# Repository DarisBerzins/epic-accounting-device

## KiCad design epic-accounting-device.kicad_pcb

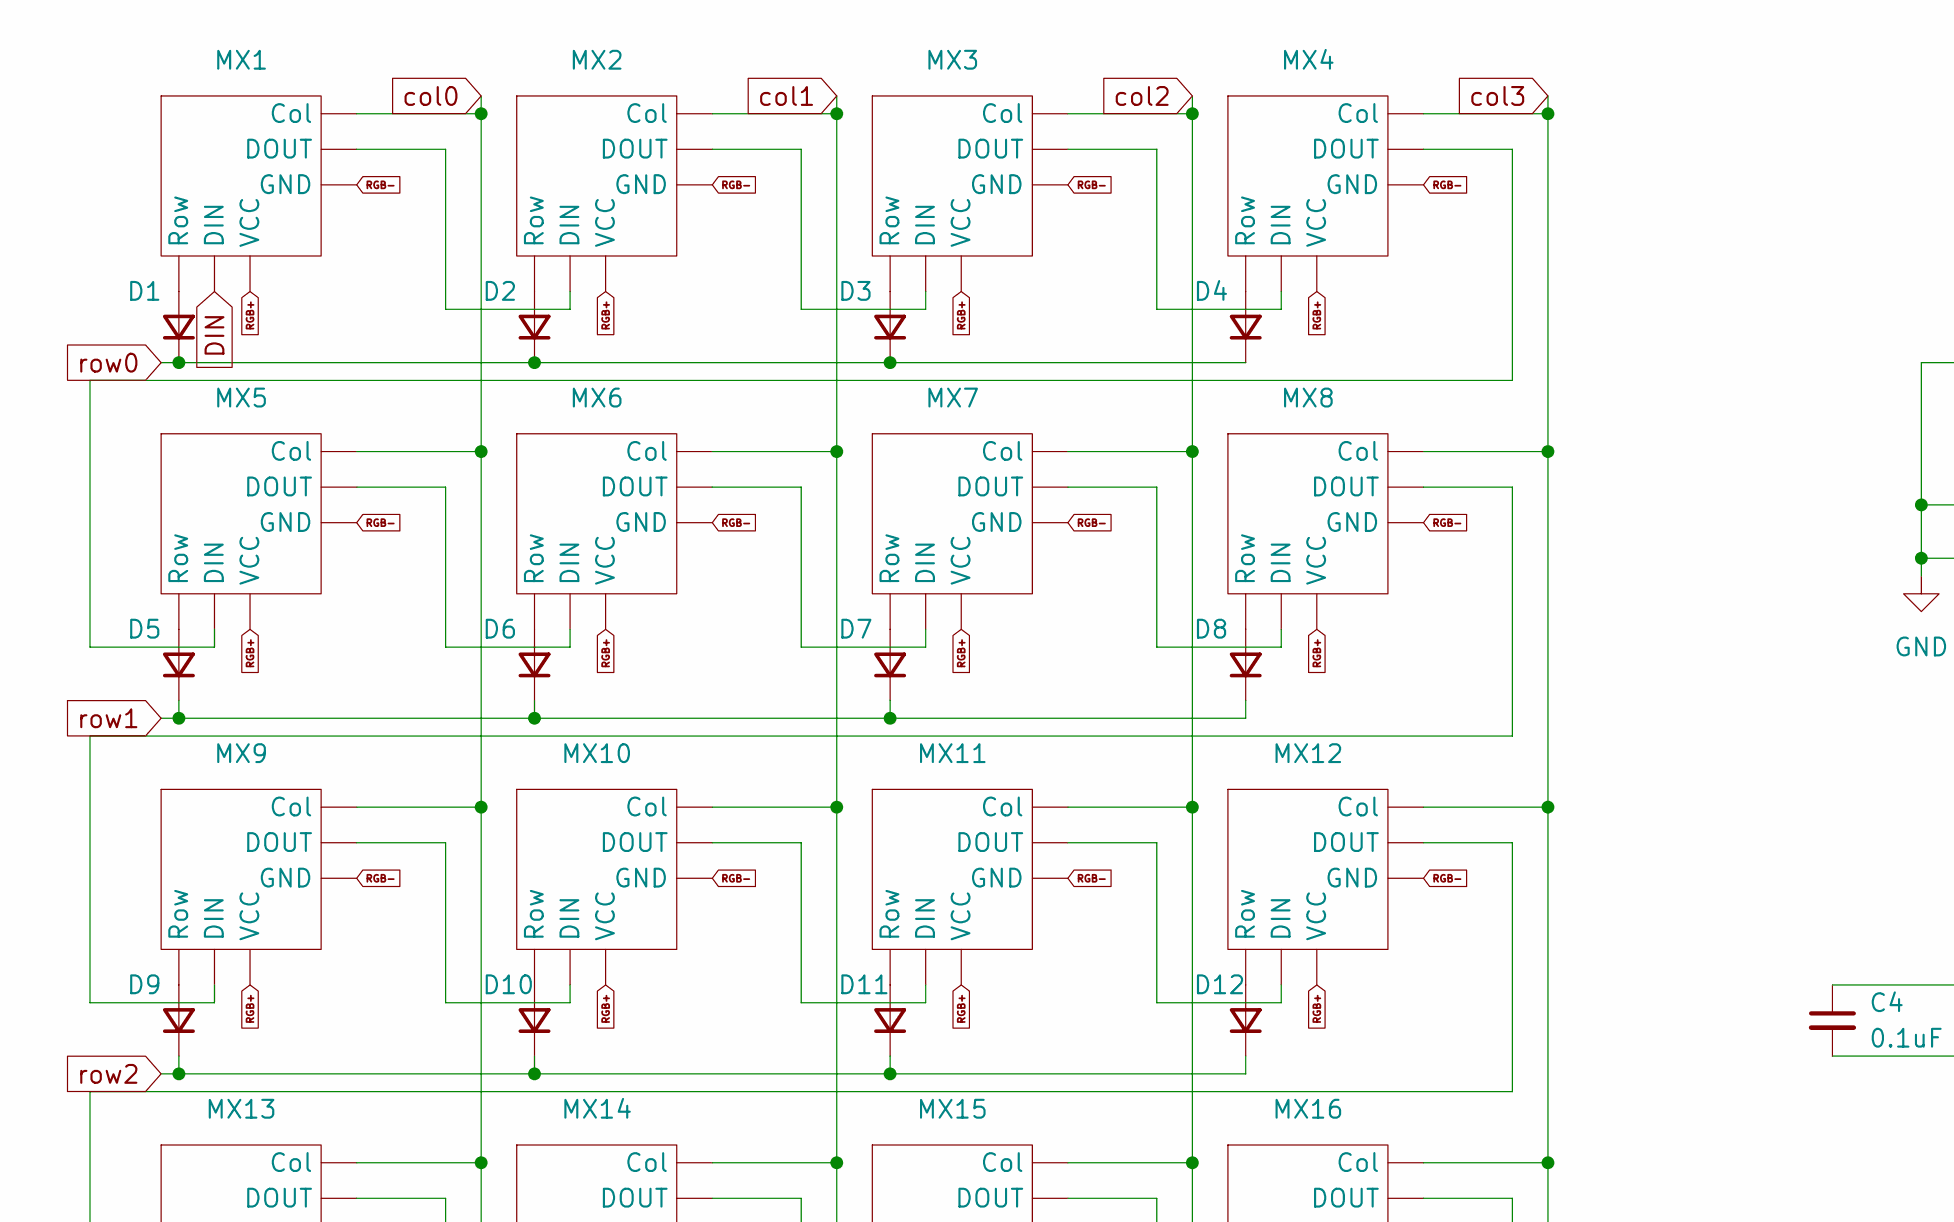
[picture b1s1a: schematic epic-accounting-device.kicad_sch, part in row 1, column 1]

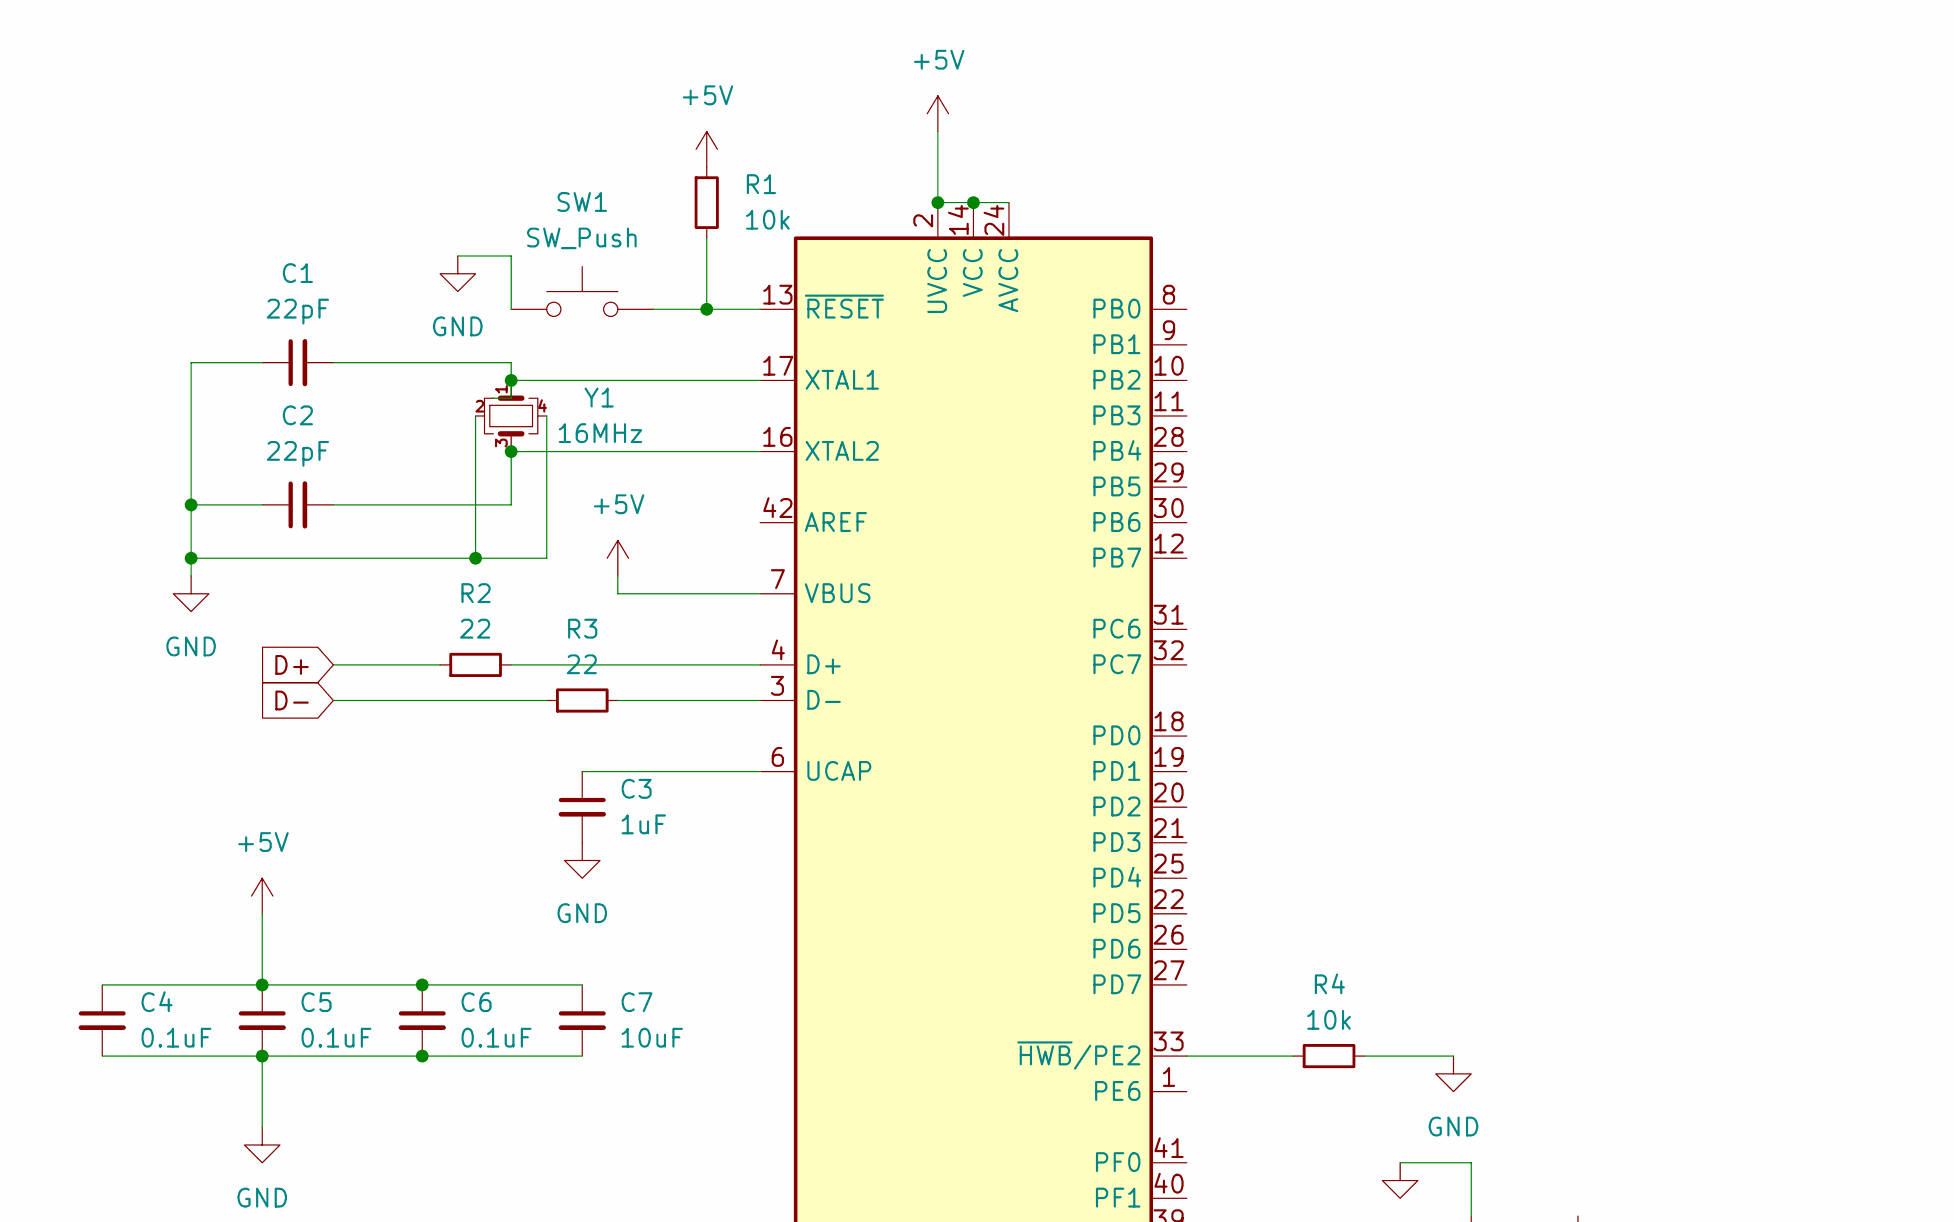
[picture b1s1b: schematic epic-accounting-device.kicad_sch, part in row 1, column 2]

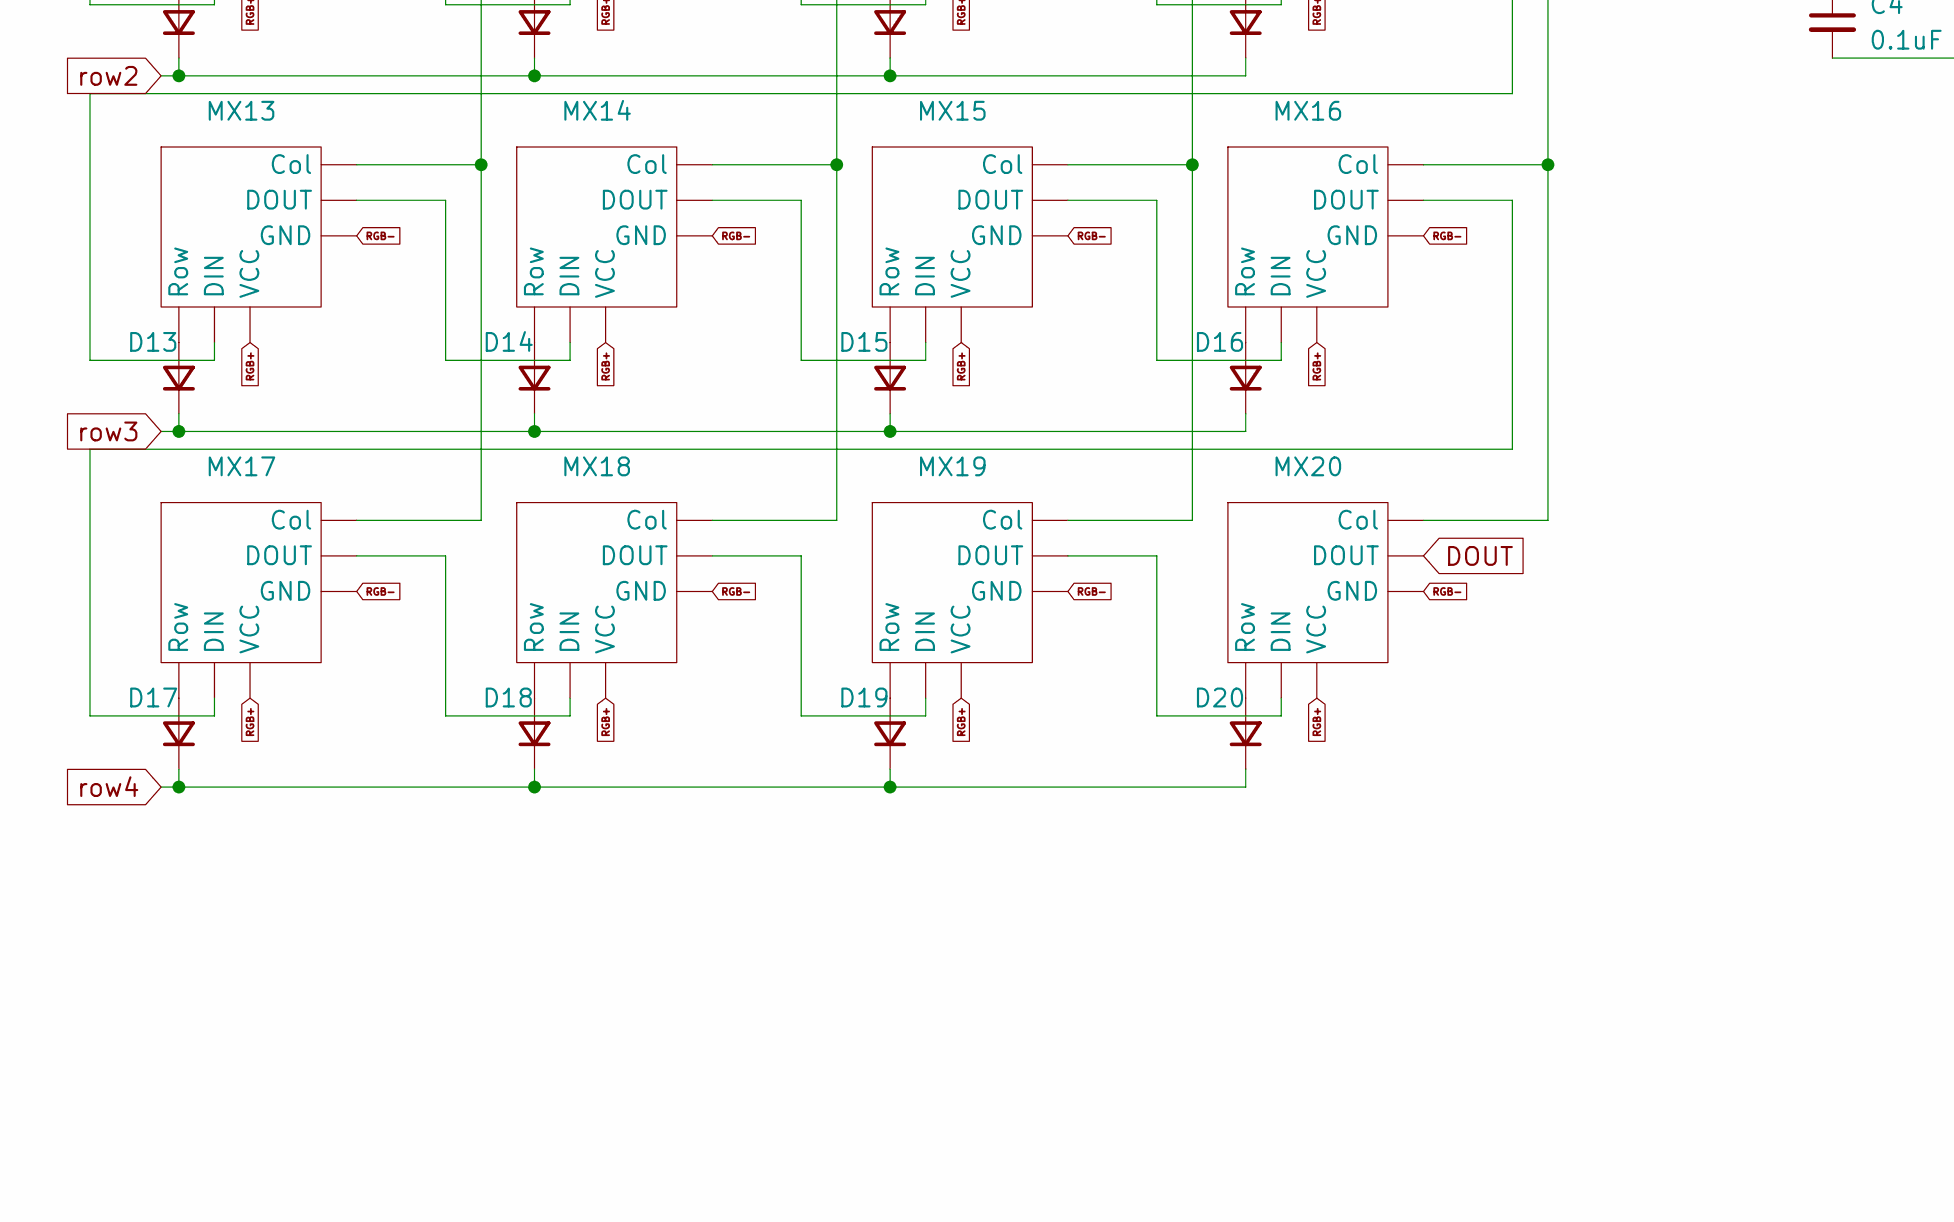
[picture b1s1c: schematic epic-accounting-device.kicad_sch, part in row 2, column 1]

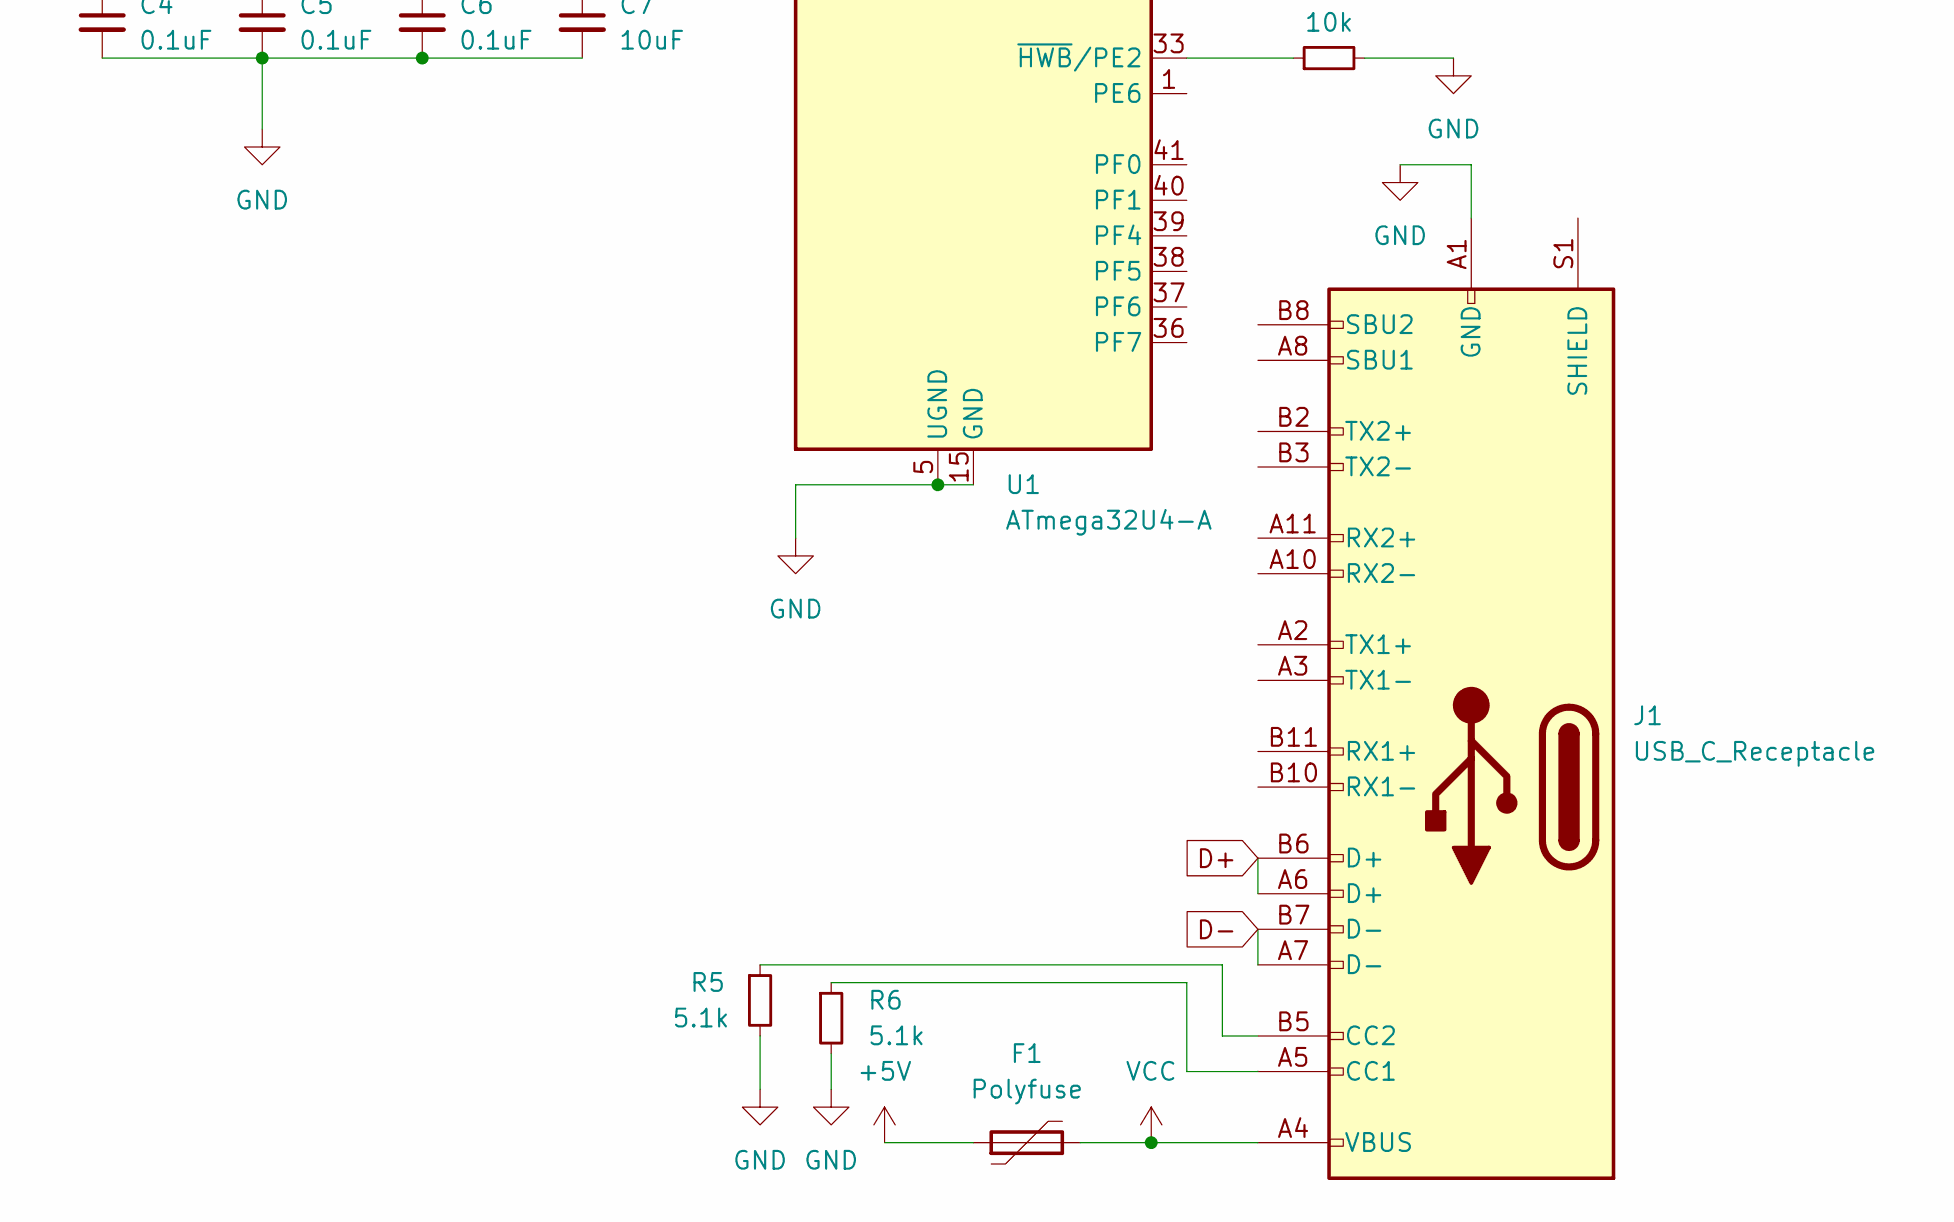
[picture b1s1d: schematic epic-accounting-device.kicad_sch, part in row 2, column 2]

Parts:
C1, C2: 22pF; C_0805_2012Metric
C3: 1uF; C_0805_2012Metric
C4, C5, C6: 0.1uF; C_0805_2012Metric
C7: 10uF; C_0805_2012Metric
D1, D2, D3, D4, D5, D6, D7, D8, D9, D10, D11, D12, D13, D14, D15, D16, D17, D18, D19, D20: D_Small; D_SOD-123
F1: Polyfuse; Fuse_1206_3216Metric
J1: USB_C_Receptacle; USB_C_Plug_Molex_105444
MX1, MX2, MX3, MX4, MX5, MX6, MX7, MX8, MX9, MX10, MX11, MX12, MX13, MX14, MX15, MX16, MX17, MX18, MX19, MX20: Cherry-MX_PCB-Mounted_LTST-A683CEGBW_Kailh_Socket
R1, R4: 10k; R_0805_2012Metric
R2, R3: 22; R_0805_2012Metric
R5, R6: 5.1k; R_0805_2012Metric
SW1: SW_Push; SKQG-1155865
U1: ATmega32U4-A; TQFP-44_10x10mm_P0.8mm
Y1: 16MHz; Crystal_SMD_3225-4Pin_3.2x2.5mm

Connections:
+5V: C4.1, C5.1, C6.1, C7.1, F1.1, R1.1, U1.2 (UVCC), U1.7 (VBUS), U1.14 (VCC), U1.24 (AVCC), U1.34 (VCC), U1.44 (AVCC)
D+: J1.A6 (D+), J1.B6 (D+), R2.1
D-: J1.A7 (D-), J1.B7 (D-), R3.1
DIN: MX1.2 (DIN)
DOUT: MX20.3 (DOUT)
GND: C1.1, C2.1, C3.2, C4.2, C5.2, C6.2, C7.2, J1.A1 (GND), J1.A12 (GND), J1.B1 (GND), J1.B12 (GND), R4.2, R5.2, R6.2, SW1.1, U1.5 (UGND), U1.15 (GND), U1.23 (GND), U1.35 (GND), U1.43 (GND), Y1.2, Y1.4
unnamed: D1.2 (A), MX1.5 (Row)
unnamed: D2.2 (A), MX2.5 (Row)
unnamed: D3.2 (A), MX3.5 (Row)
unnamed: D4.2 (A), MX4.5 (Row)
unnamed: D5.2 (A), MX5.5 (Row)
unnamed: D6.2 (A), MX6.5 (Row)
unnamed: D7.2 (A), MX7.5 (Row)
unnamed: D8.2 (A), MX8.5 (Row)
unnamed: D9.2 (A), MX9.5 (Row)
unnamed: D10.2 (A), MX10.5 (Row)
unnamed: D11.2 (A), MX11.5 (Row)
unnamed: D12.2 (A), MX12.5 (Row)
unnamed: D13.2 (A), MX13.5 (Row)
unnamed: D14.2 (A), MX14.5 (Row)
unnamed: D15.2 (A), MX15.5 (Row)
unnamed: D16.2 (A), MX16.5 (Row)
unnamed: D17.2 (A), MX17.5 (Row)
unnamed: D18.2 (A), MX18.5 (Row)
unnamed: D19.2 (A), MX19.5 (Row)
unnamed: D20.2 (A), MX20.5 (Row)
unnamed: J1.A5 (CC1), R6.1
unnamed: J1.B5 (CC2), R5.1
unnamed: MX1.3 (DOUT), MX2.2 (DIN)
unnamed: MX2.3 (DOUT), MX3.2 (DIN)
unnamed: MX3.3 (DOUT), MX4.2 (DIN)
unnamed: MX4.3 (DOUT), MX5.2 (DIN)
unnamed: MX5.3 (DOUT), MX6.2 (DIN)
unnamed: MX6.3 (DOUT), MX7.2 (DIN)
unnamed: MX7.3 (DOUT), MX8.2 (DIN)
unnamed: MX8.3 (DOUT), MX9.2 (DIN)
unnamed: MX9.3 (DOUT), MX10.2 (DIN)
unnamed: MX10.3 (DOUT), MX11.2 (DIN)
unnamed: MX11.3 (DOUT), MX12.2 (DIN)
unnamed: MX12.3 (DOUT), MX13.2 (DIN)
unnamed: MX13.3 (DOUT), MX14.2 (DIN)
unnamed: MX14.3 (DOUT), MX15.2 (DIN)
unnamed: MX15.3 (DOUT), MX16.2 (DIN)
unnamed: MX16.3 (DOUT), MX17.2 (DIN)
unnamed: MX17.3 (DOUT), MX18.2 (DIN)
unnamed: MX18.3 (DOUT), MX19.2 (DIN)
unnamed: MX19.3 (DOUT), MX20.2 (DIN)
unnamed: R2.2, U1.4 (D+)
unnamed: R3.2, U1.3 (D-)
unnamed: C3.1, U1.6 (UCAP)
unnamed: C1.2, U1.17 (XTAL1), Y1.1
unnamed: C2.2, U1.16 (XTAL2), Y1.3
unnamed: R4.1, U1.33 (~HWB/PE2)
unnamed: R1.2, SW1.2, U1.13 (~RESET)
RGB+: MX1.4 (VCC), MX2.4 (VCC), MX3.4 (VCC), MX4.4 (VCC), MX5.4 (VCC), MX6.4 (VCC), MX7.4 (VCC), MX8.4 (VCC), MX9.4 (VCC), MX10.4 (VCC), MX11.4 (VCC), MX12.4 (VCC), MX13.4 (VCC), MX14.4 (VCC), MX15.4 (VCC), MX16.4 (VCC), MX17.4 (VCC), MX18.4 (VCC), MX19.4 (VCC), MX20.4 (VCC)
RGB-: MX1.1 (GND), MX2.1 (GND), MX3.1 (GND), MX4.1 (GND), MX5.1 (GND), MX6.1 (GND), MX7.1 (GND), MX8.1 (GND), MX9.1 (GND), MX10.1 (GND), MX11.1 (GND), MX12.1 (GND), MX13.1 (GND), MX14.1 (GND), MX15.1 (GND), MX16.1 (GND), MX17.1 (GND), MX18.1 (GND), MX19.1 (GND), MX20.1 (GND)
VCC: F1.2, J1.A4 (VBUS), J1.A9 (VBUS), J1.B4 (VBUS), J1.B9 (VBUS)
col0: MX1.6 (Col), MX5.6 (Col), MX9.6 (Col), MX13.6 (Col), MX17.6 (Col)
col1: MX2.6 (Col), MX6.6 (Col), MX10.6 (Col), MX14.6 (Col), MX18.6 (Col)
col2: MX3.6 (Col), MX7.6 (Col), MX11.6 (Col), MX15.6 (Col), MX19.6 (Col)
col3: MX4.6 (Col), MX8.6 (Col), MX12.6 (Col), MX16.6 (Col), MX20.6 (Col)
row0: D1.1 (K), D2.1 (K), D3.1 (K), D4.1 (K)
row1: D5.1 (K), D6.1 (K), D7.1 (K), D8.1 (K)
row2: D9.1 (K), D10.1 (K), D11.1 (K), D12.1 (K)
row3: D13.1 (K), D14.1 (K), D15.1 (K), D16.1 (K)
row4: D17.1 (K), D18.1 (K), D19.1 (K), D20.1 (K)

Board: 2 copper layers, 57 parts (0 on the bottom side), 64 nets, no tracks yet.
